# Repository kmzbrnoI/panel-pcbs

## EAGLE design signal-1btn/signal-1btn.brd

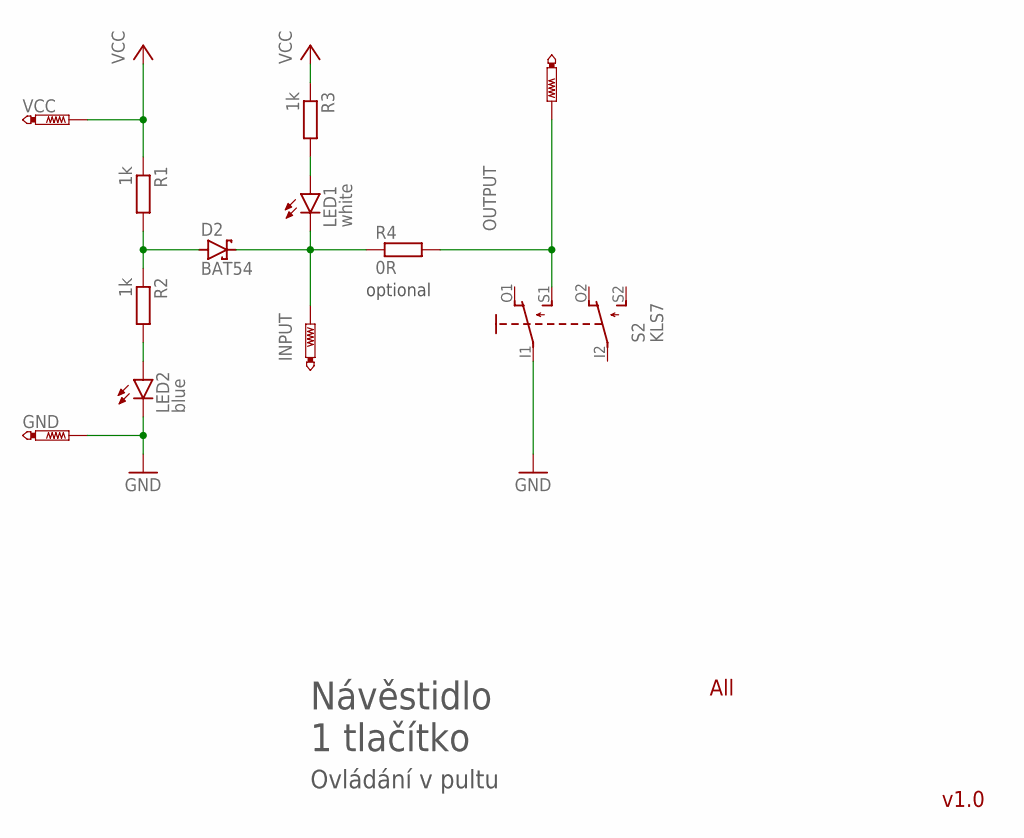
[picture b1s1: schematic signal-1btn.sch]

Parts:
D2: BAT54; SOT23
GND: PTR1PAD1-13Y; P1-13Y
LED1: white; LED3MM
LED2: blue; LED3MM
P_ACTIVE, P_ACTIVE1: PTR1PAD1-13Y; P1-13Y
R1, R2, R3: 1k; R0805
R4: 0R; R0805
S2: KLS7
VCC: PTR1PAD1-13Y; P1-13Y

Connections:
GND: GND.TP, LED2.K (C), S2.I1
INPUT: D2.3 (C), LED1.K (C), P_ACTIVE1.TP, R4.1
unnamed: LED2.A, R2.2
unnamed: D2.1 (A), R1.2, R2.1
unnamed: LED1.A, R3.2
OUTPUT: P_ACTIVE.TP, R4.2, S2.S1 (S)
VCC: R1.1, R3.1, VCC.TP

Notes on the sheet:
Návěstidlo 1 tlačítko
v1.0
All
Ovládání v pultu
optional

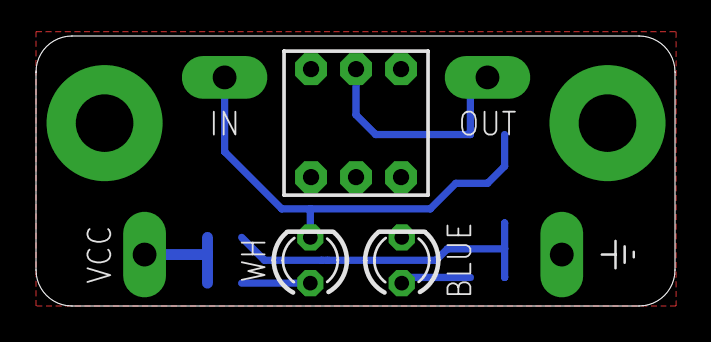
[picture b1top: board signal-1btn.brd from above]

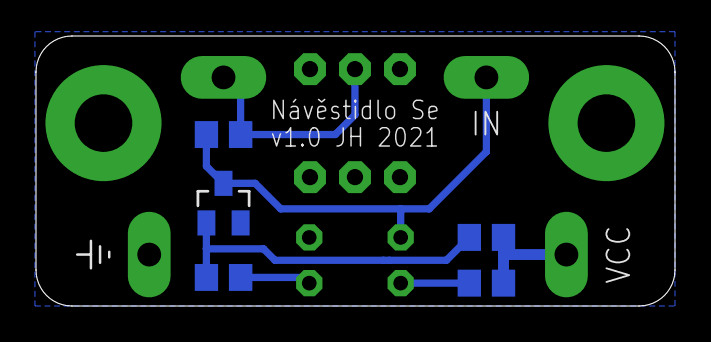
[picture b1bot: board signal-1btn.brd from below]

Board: 2 copper layers, 35.5 x 15.0 mm, 12 parts (5 on the bottom side), 7 nets.

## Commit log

2021-11-06 Add Eagle .gitignore.
2021-11-06 Add all PCBs.
2021-11-06 Add Se signal PCB.
2021-11-07 gitignore kicad files.
2021-11-07 Add signal-1btn schematics in kicad.
2021-11-07 Add KLS7 switch library
2021-11-07 Update kicad .gitignore.
2021-11-07 Add signal-1btn-kicad PCB.
2021-11-07 Add Makefile for panelization & production data.
2021-11-07 Add texts, use 2×5 panel.
2021-11-09 Import signal to turnout-single.
2021-11-09 Add turnout schematics.
2021-11-09 Add turnout-single pcb.
2021-11-09 Add solder-jumpers for connecting inputs & outputs.
2021-11-09 Add description as plain texts.
2021-11-09 Remove Cu from around mounting holes.
2021-11-10 Use mounting holes without Cu.
2021-11-10 Add single button pcb.
2021-11-10 Add double-turnout PCB.
2021-11-10 Change panelization to mousebites.
2021-11-10 single-button: add nice panel parameters.
2021-11-10 Single-button: add pads to other side to make mounting easier.
2021-11-23 Add signal-square PCB.
2021-11-24 Turnout-double: add mounting holes clearance.
2021-11-28 Update turnout-single.
2021-11-28 Use negative offset in mousebites panelization.
2021-12-16 Fix BAT54 package (SOT23).
2021-12-16 Fix package.
2021-12-16 Signal: switch diodes.
2021-12-16 Turnout-double: allow both side placement.
2021-12-17 Turnout-double: dubplicate parts.
    To allow mirror placement on panel.
2021-12-17 Add 2btn2leds pcb.
2022-01-12 Add missing wire.
2022-01-27 turnout-double: migrate to KiCad 6.
2022-01-27 turnout-double: add wires for reversed placing.
2022-01-27 turnout-double: add author & version to silkscreen.
2022-01-27 turnout-single: update to KiCad 6.
2022-01-27 Add turnout-crossing.
